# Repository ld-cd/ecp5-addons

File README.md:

# ECP5 Addons

A random set of addon boards designed for the Lattice ECP5-EVAL board.

## Cape

So far the only addon is the cape in the folder cape/
This adds support for up to two 256Mb SDRAM's, an SD Card, and a Micro USB port that'll hopefully be able to push USB Full Speed.

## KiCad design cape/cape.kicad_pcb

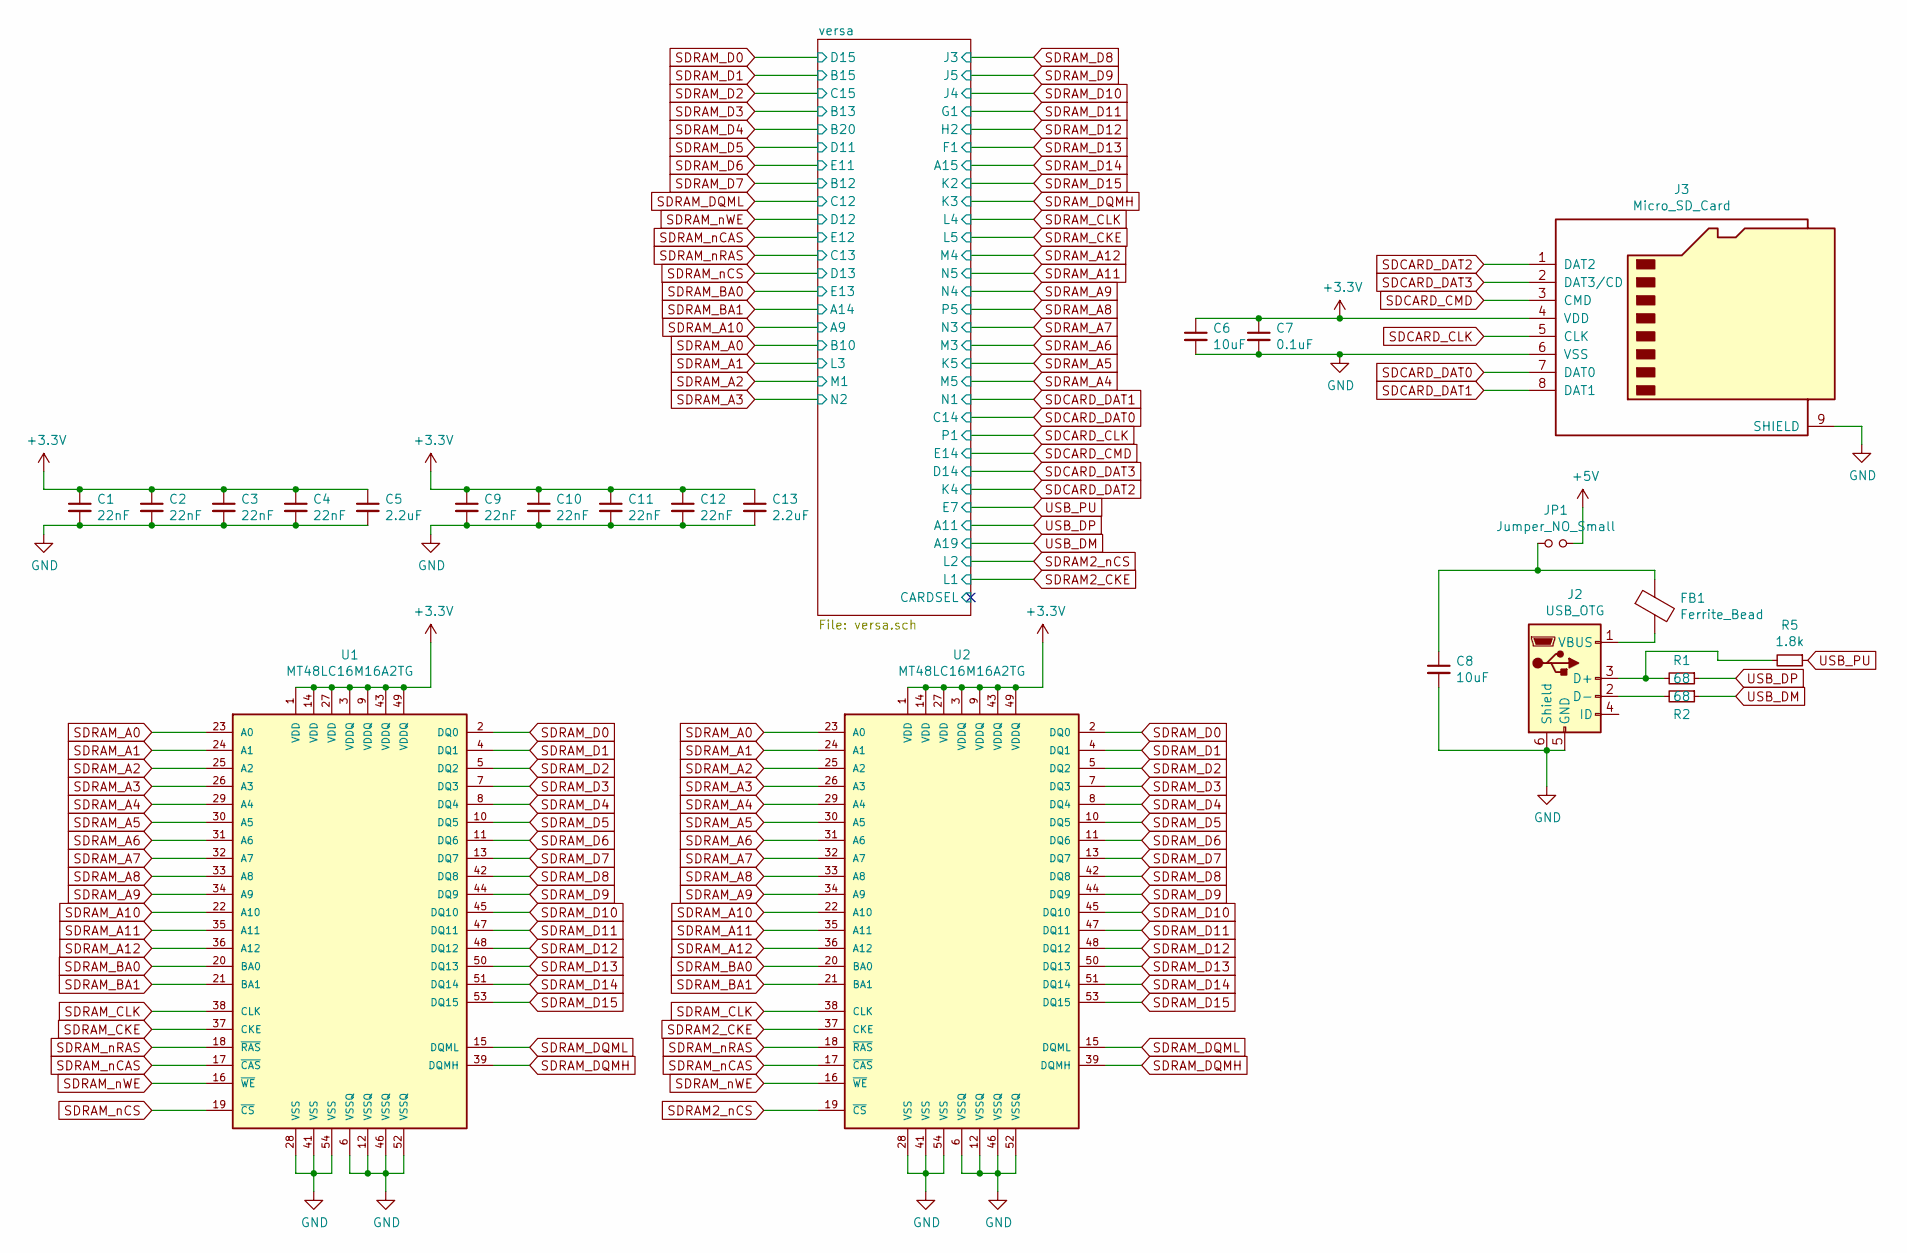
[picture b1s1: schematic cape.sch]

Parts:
C1, C2, C3, C4, C9, C10, C11, C12: 22nF; C_0603_1608Metric_Pad1.05x0.95mm_HandSolder
C5, C13: 2.2uF; C_0603_1608Metric_Pad1.05x0.95mm_HandSolder
C6, C8: 10uF; C_0603_1608Metric_Pad1.05x0.95mm_HandSolder
C7: 0.1uF; C_0603_1608Metric_Pad1.05x0.95mm_HandSolder
FB1: Ferrite_Bead; L_0603_1608Metric_Pad1.05x0.95mm_HandSolder
J2: USB_OTG; USB_Micro-B_Molex-105017-0001
J3: Micro_SD_Card; microSD_HC_Wuerth_693072010801
JP1: Jumper_NO_Small; SolderJumper-2_P1.3mm_Open_Pad1.0x1.5mm
R1, R2: 68; R_0603_1608Metric_Pad1.05x0.95mm_HandSolder
R5: 1.8k; R_0603_1608Metric_Pad1.05x0.95mm_HandSolder
U1, U2: MT48LC16M16A2TG; TSOP54

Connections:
+3V3: C1.1, C2.1, C3.1, C4.1, C5.1, C6.1, C7.1, C9.1, C10.1, C11.1, C12.1, C13.1, J3.4 (VDD), U1.1 (VDD), U1.3 (VDDQ), U1.9 (VDDQ), U1.14 (VDD), U1.27 (VDD), U1.43 (VDDQ), U1.49 (VDDQ), U2.1 (VDD), U2.3 (VDDQ), U2.9 (VDDQ), U2.14 (VDD), U2.27 (VDD), U2.43 (VDDQ), U2.49 (VDDQ); also elsewhere on the board
+5V: JP1.2; also elsewhere on the board
GND: C1.2, C2.2, C3.2, C4.2, C5.2, C6.2, C7.2, C8.2, C9.2, C10.2, C11.2, C12.2, C13.2, J2.5 (GND), J2.6 (Shield), J3.6 (VSS), J3.9 (SHIELD), U1.6 (VSSQ), U1.12 (VSSQ), U1.28 (VSS), U1.41 (VSS), U1.46 (VSSQ), U1.52 (VSSQ), U1.54 (VSS), U2.6 (VSSQ), U2.12 (VSSQ), U2.28 (VSS), U2.41 (VSS), U2.46 (VSSQ), U2.52 (VSSQ), U2.54 (VSS); also elsewhere on the board
unnamed: C8.1, FB1.1, JP1.1
unnamed: FB1.2, J2.1 (VBUS)
unnamed: J2.2 (D-), R2.2
unnamed: J2.3 (D+), R1.2, R5.2
SDCARD_CLK: J3.5 (CLK); also elsewhere on the board
SDCARD_CMD: J3.3 (CMD); also elsewhere on the board
SDCARD_DAT0: J3.7 (DAT0); also elsewhere on the board
SDCARD_DAT1: J3.8 (DAT1); also elsewhere on the board
SDCARD_DAT2: J3.1 (DAT2); also elsewhere on the board
SDCARD_DAT3: J3.2 (DAT3/CD); also elsewhere on the board
SDRAM2_CKE: U2.37 (CKE); also elsewhere on the board
SDRAM2_nCS: U2.19 (~CS~); also elsewhere on the board
SDRAM_A0: U1.23 (A0), U2.23 (A0); also elsewhere on the board
SDRAM_A1: U1.24 (A1), U2.24 (A1); also elsewhere on the board
SDRAM_A2: U1.25 (A2), U2.25 (A2); also elsewhere on the board
SDRAM_A3: U1.26 (A3), U2.26 (A3); also elsewhere on the board
SDRAM_A4: U1.29 (A4), U2.29 (A4); also elsewhere on the board
SDRAM_A5: U1.30 (A5), U2.30 (A5); also elsewhere on the board
SDRAM_A6: U1.31 (A6), U2.31 (A6); also elsewhere on the board
SDRAM_A7: U1.32 (A7), U2.32 (A7); also elsewhere on the board
SDRAM_A8: U1.33 (A8), U2.33 (A8); also elsewhere on the board
SDRAM_A9: U1.34 (A9), U2.34 (A9); also elsewhere on the board
SDRAM_A10: U1.22 (A10), U2.22 (A10); also elsewhere on the board
SDRAM_A11: U1.35 (A11), U2.35 (A11); also elsewhere on the board
SDRAM_A12: U1.36 (A12), U2.36 (A12); also elsewhere on the board
SDRAM_BA0: U1.20 (BA0), U2.20 (BA0); also elsewhere on the board
SDRAM_BA1: U1.21 (BA1), U2.21 (BA1); also elsewhere on the board
SDRAM_CKE: U1.37 (CKE); also elsewhere on the board
SDRAM_CLK: U1.38 (CLK), U2.38 (CLK); also elsewhere on the board
SDRAM_D0: U1.2 (DQ0), U2.2 (DQ0); also elsewhere on the board
SDRAM_D1: U1.4 (DQ1), U2.4 (DQ1); also elsewhere on the board
SDRAM_D2: U1.5 (DQ2), U2.5 (DQ2); also elsewhere on the board
SDRAM_D3: U1.7 (DQ3), U2.7 (DQ3); also elsewhere on the board
SDRAM_D4: U1.8 (DQ4), U2.8 (DQ4); also elsewhere on the board
SDRAM_D5: U1.10 (DQ5), U2.10 (DQ5); also elsewhere on the board
SDRAM_D6: U1.11 (DQ6), U2.11 (DQ6); also elsewhere on the board
SDRAM_D7: U1.13 (DQ7), U2.13 (DQ7); also elsewhere on the board
SDRAM_D8: U1.42 (DQ8), U2.42 (DQ8); also elsewhere on the board
SDRAM_D9: U1.44 (DQ9), U2.44 (DQ9); also elsewhere on the board
SDRAM_D10: U1.45 (DQ10), U2.45 (DQ10); also elsewhere on the board
SDRAM_D11: U1.47 (DQ11), U2.47 (DQ11); also elsewhere on the board
SDRAM_D12: U1.48 (DQ12), U2.48 (DQ12); also elsewhere on the board
SDRAM_D13: U1.50 (DQ13), U2.50 (DQ13); also elsewhere on the board
SDRAM_D14: U1.51 (DQ14), U2.51 (DQ14); also elsewhere on the board
SDRAM_D15: U1.53 (DQ15), U2.53 (DQ15); also elsewhere on the board
SDRAM_DQMH: U1.39 (DQMH), U2.39 (DQMH); also elsewhere on the board
SDRAM_DQML: U1.15 (DQML), U2.15 (DQML); also elsewhere on the board
SDRAM_nCAS: U1.17 (~CAS~), U2.17 (~CAS~); also elsewhere on the board
SDRAM_nCS: U1.19 (~CS~); also elsewhere on the board
SDRAM_nRAS: U1.18 (~RAS~), U2.18 (~RAS~); also elsewhere on the board
SDRAM_nWE: U1.16 (~WE~), U2.16 (~WE~); also elsewhere on the board
USB_DM: R2.1; also elsewhere on the board
USB_DP: R1.1; also elsewhere on the board
USB_PU: R5.1; also elsewhere on the board

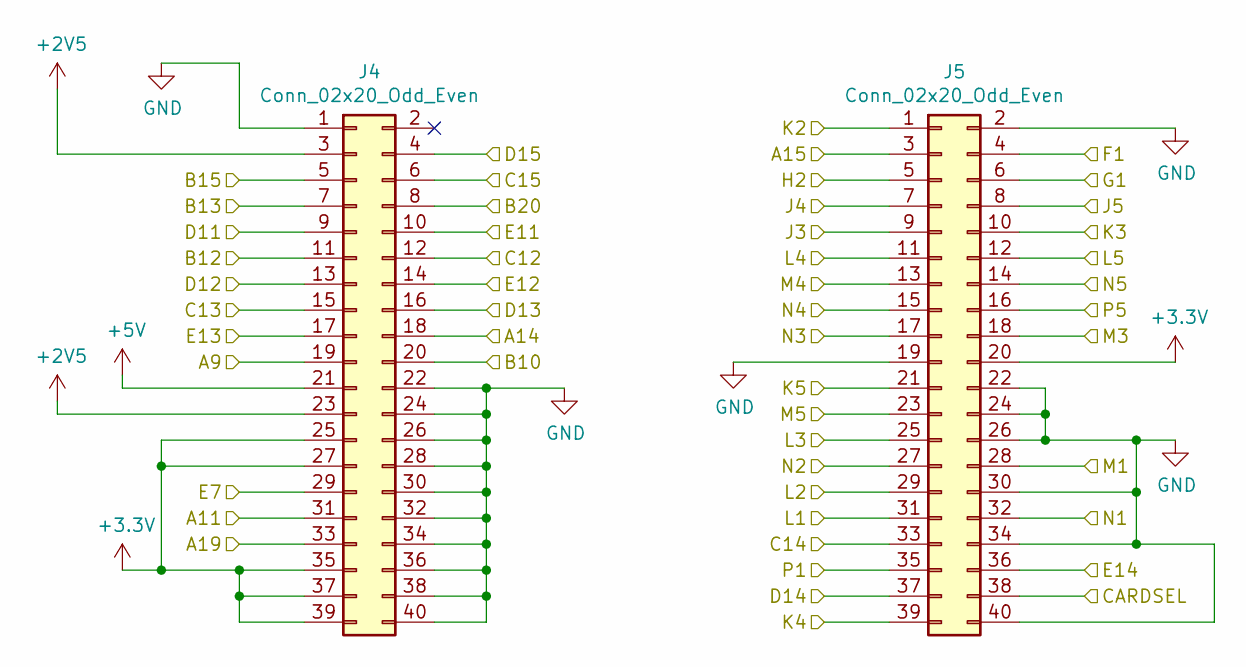
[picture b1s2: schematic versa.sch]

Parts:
J4, J5: Conn_02x20_Odd_Even; PinHeader_2x20_P2.54mm_Vertical

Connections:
+2V5: J4.3, J4.23
+3V3: J4.25, J4.27, J4.35, J4.37, J4.39, J5.20; also elsewhere on the board
+5V: J4.21; also elsewhere on the board
/versa/CARDSEL: J5.38
GND: J4.1, J4.22, J4.24, J4.26, J4.28, J4.30, J4.32, J4.34, J4.36, J4.38, J4.40, J5.2, J5.19, J5.22, J5.24, J5.26, J5.30, J5.34, J5.40; also elsewhere on the board
SDCARD_CLK: J5.35; also elsewhere on the board
SDCARD_CMD: J5.36; also elsewhere on the board
SDCARD_DAT0: J5.33; also elsewhere on the board
SDCARD_DAT1: J5.32; also elsewhere on the board
SDCARD_DAT2: J5.39; also elsewhere on the board
SDCARD_DAT3: J5.37; also elsewhere on the board
SDRAM2_CKE: J5.31; also elsewhere on the board
SDRAM2_nCS: J5.29; also elsewhere on the board
SDRAM_A0: J4.20; also elsewhere on the board
SDRAM_A1: J5.25; also elsewhere on the board
SDRAM_A2: J5.28; also elsewhere on the board
SDRAM_A3: J5.27; also elsewhere on the board
SDRAM_A4: J5.23; also elsewhere on the board
SDRAM_A5: J5.21; also elsewhere on the board
SDRAM_A6: J5.18; also elsewhere on the board
SDRAM_A7: J5.17; also elsewhere on the board
SDRAM_A8: J5.16; also elsewhere on the board
SDRAM_A9: J5.15; also elsewhere on the board
SDRAM_A10: J4.19; also elsewhere on the board
SDRAM_A11: J5.14; also elsewhere on the board
SDRAM_A12: J5.13; also elsewhere on the board
SDRAM_BA0: J4.17; also elsewhere on the board
SDRAM_BA1: J4.18; also elsewhere on the board
SDRAM_CKE: J5.12; also elsewhere on the board
SDRAM_CLK: J5.11; also elsewhere on the board
SDRAM_D0: J4.4; also elsewhere on the board
SDRAM_D1: J4.5; also elsewhere on the board
SDRAM_D2: J4.6; also elsewhere on the board
SDRAM_D3: J4.7; also elsewhere on the board
SDRAM_D4: J4.8; also elsewhere on the board
SDRAM_D5: J4.9; also elsewhere on the board
SDRAM_D6: J4.10; also elsewhere on the board
SDRAM_D7: J4.11; also elsewhere on the board
SDRAM_D8: J5.9; also elsewhere on the board
SDRAM_D9: J5.8; also elsewhere on the board
SDRAM_D10: J5.7; also elsewhere on the board
SDRAM_D11: J5.6; also elsewhere on the board
SDRAM_D12: J5.5; also elsewhere on the board
SDRAM_D13: J5.4; also elsewhere on the board
SDRAM_D14: J5.3; also elsewhere on the board
SDRAM_D15: J5.1; also elsewhere on the board
SDRAM_DQMH: J5.10; also elsewhere on the board
SDRAM_DQML: J4.12; also elsewhere on the board
SDRAM_nCAS: J4.14; also elsewhere on the board
SDRAM_nCS: J4.16; also elsewhere on the board
SDRAM_nRAS: J4.15; also elsewhere on the board
SDRAM_nWE: J4.13; also elsewhere on the board
USB_DM: J4.33; also elsewhere on the board
USB_DP: J4.31; also elsewhere on the board
USB_PU: J4.29; also elsewhere on the board

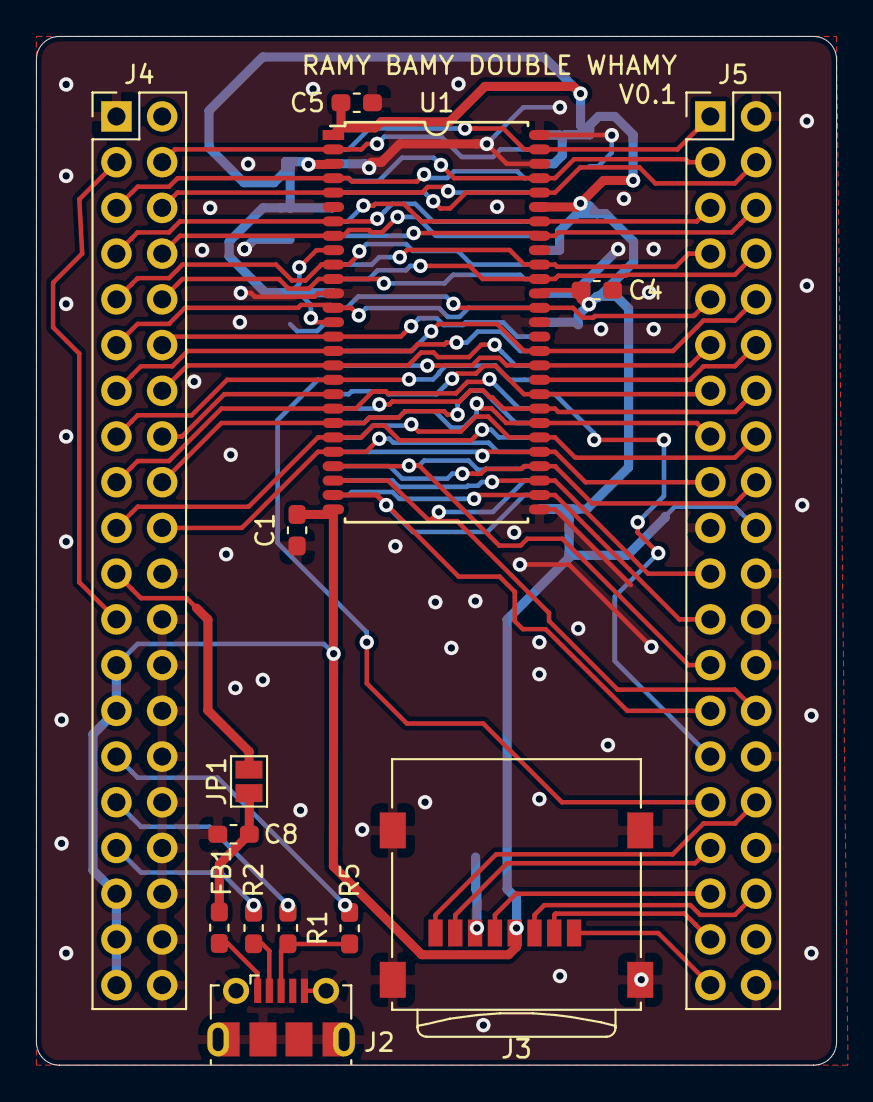
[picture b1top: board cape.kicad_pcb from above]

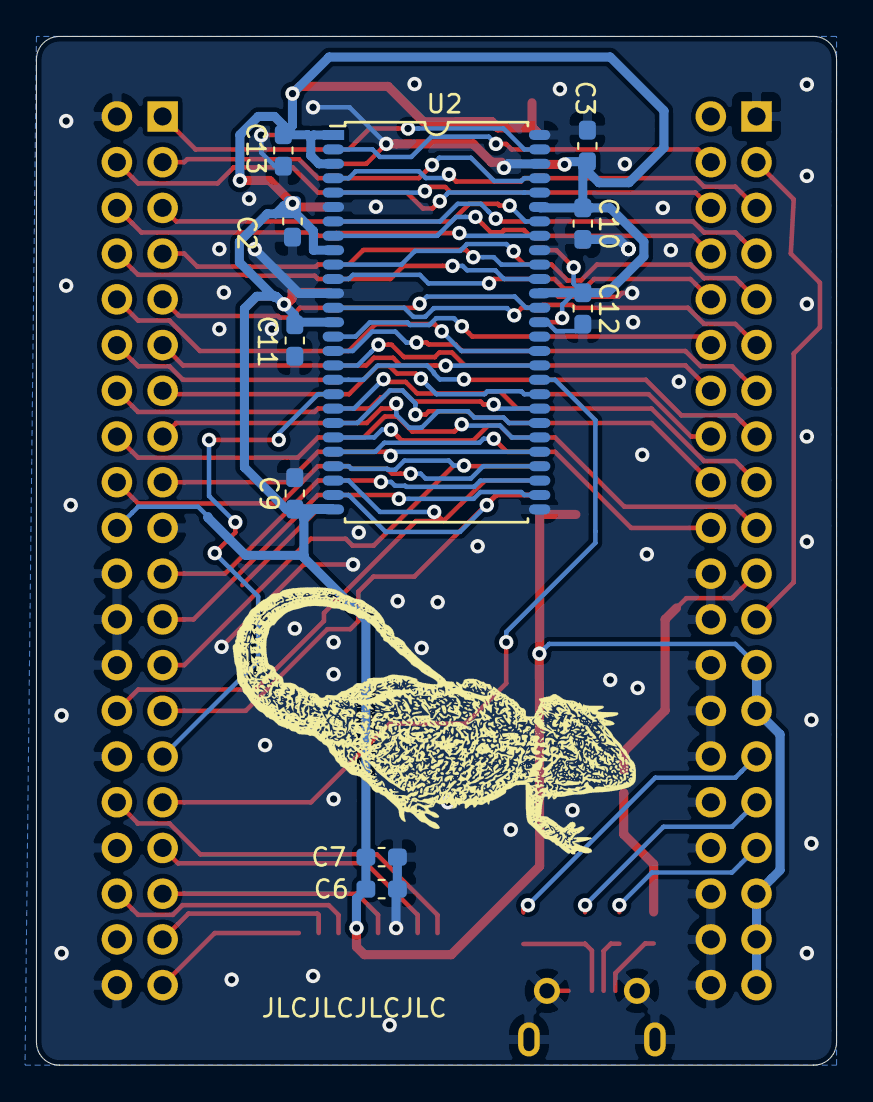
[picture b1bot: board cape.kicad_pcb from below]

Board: 2 copper layers, 44.5 x 57.2 mm, 24 parts (10 on the bottom side), 58 nets.

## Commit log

2020-03-09 initial_commit
2020-03-09 floof
